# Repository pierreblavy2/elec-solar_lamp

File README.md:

# Features
* A cheap very simple solar lamp. Can be 3D printed, or built in a glass jar.
* Automatically switch on/of the light when night/day comes
* Solar
* Can be switched off manualy, and used as a torch
* Printable circuit board (KiCad), can easily be done on perfboard too.

# Pictures

# Components

|Name|Quantity|Description|
|---|---|---|
|QX5252|1|https://datasheetspdf.com/pdf/719492/Qxmd/QX5252/1|
|AAA_holder|1|AAA battery holder|
|Solar_panel|1|60x60 mm, 5V|
|5mm LED|1|20mA LED|
|330uH|1|Inductance DIP (1)|
|Switch|1|20mm, toggle, on/off (2)|
|5mm LED support|1|RTM5021|

(1) Inductance values control the currant going trough the LED, according to this table. The default value is 330 uH. Lower inductince will increase light brightness and decrease battery duration.

|Inductance (uH)|Current (mA)|
|---|---|
|330|11|
|270|14.5|
|220|15.5|
|150|25|
|100|34.5|
|82|38|
|56|50|
|47|75|
|33|110|

(2) The switch is mounted in series with the LED

# Circuit

# License
This project is licensed under the [LGPL-v3 license](https://www.gnu.org/licenses/lgpl-3.0.txt).

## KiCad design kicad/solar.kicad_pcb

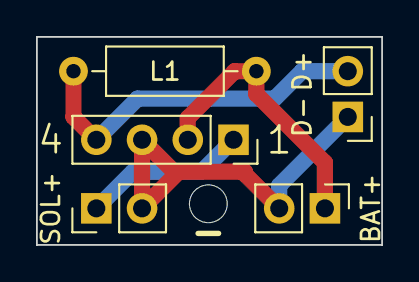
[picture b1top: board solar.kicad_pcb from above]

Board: 2 copper layers, 19.2 x 11.6 mm, 5 parts (0 on the bottom side), 4 nets.

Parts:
1: QX5252; PinSocket_1x04_P2.54mm_Vertical
BT1: Battery_Cell; PinHeader_1x02_P2.54mm_Vertical
D1: LED; PinHeader_1x02_P2.54mm_Vertical
L1: L; R_Axial_DIN0207_L6.3mm_D2.5mm_P10.16mm_Horizontal
SC1: Solar_Cell; PinHeader_1x02_P2.54mm_Vertical

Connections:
GND: 1.3 (VSS), BT1.2 (-), D1.1 (K), SC1.2 (-)
unnamed: 1.2 (BAT), BT1.1 (+), L1.1
unnamed: 1.4 (LX), D1.2 (A), L1.2
unnamed: 1.1 (SBAT), SC1.1 (+)

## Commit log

2022-12-03 Create LICENSE
